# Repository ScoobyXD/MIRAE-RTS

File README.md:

MIRAE RTS

Turn everything into an rts game

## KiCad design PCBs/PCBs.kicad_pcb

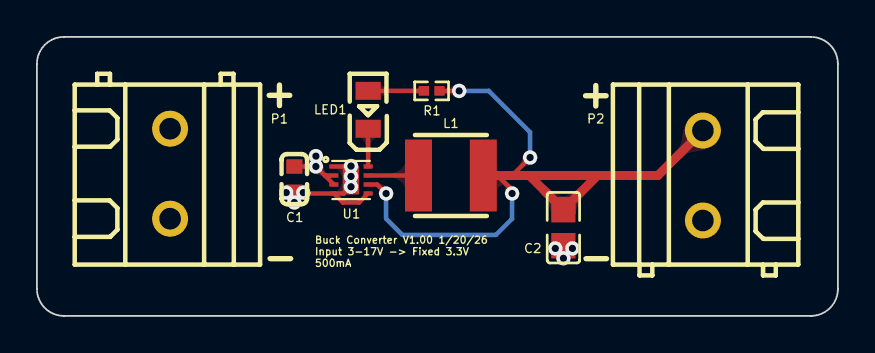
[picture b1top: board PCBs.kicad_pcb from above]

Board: 4 copper layers, 44.5 x 15.5 mm, 8 parts (0 on the bottom side), 6 nets.

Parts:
C1: 10 uF; C0603
C2: 22 uF; C0805
L1: 2.2uH; IND-SMD_L4.0-W4.0_LQH44PN2R2MP0L
LED1: Green LED; LED0805-R-RD
P1: Input 1x2; CONN-TH_2P-P5.00_WJ128V-5.0-2P
P2: Output 1x2; CONN-TH_2P-P5.00_WJ128V-5.0-2P
R1: 100k Ohms; R0402
U1: TPS62172DSGR; WSON-8_L2.0-W2.0-P0.50-TL-EP

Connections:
GND: C1.1, C2.2, P1.2, P2.1, U1.1 (PGND), U1.4 (AGND), U1.5 (FB), U1.9 (EP)
unnamed: LED1.1 (A), R1.1
unnamed: LED1.2 (K), U1.8 (PG)
unnamed: L1.2, U1.7 (SW)
VCCIN: C1.2, P1.1, U1.2 (VIN), U1.3 (EN)
VCCOUT: C2.1, L1.1, P2.2, R1.2, U1.6 (VOS)

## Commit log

2025-12-20 esp-idf hello world template
2026-01-09 Update README with project description
    Add project description to README
2026-01-09 Update project name and description in README
2026-01-09 click drag works
2026-01-11 last commit before going to internet
2026-01-19 buck converter schematic
2026-01-19 trace
2026-01-19 buck converter
2026-01-20 vias under pads and other changes
2026-01-21 changes for easyeda components
2026-01-21 should be done
2026-01-21 done
2026-01-21 buck converter done
2026-01-21 imported old wheelson stm32 project
2026-01-21 original stm32 file
2026-01-23 led on
2026-01-24 rtos led blink
2026-01-24 set clocks
2026-01-24 heartbeat 80Mhz RTOS
2026-01-25 basic i2c config, doesnt work yet
2026-01-25 what i have before clause opus
2026-01-26 i2c in progress
2026-01-27 working on i2c
2026-01-28 holy debug
2026-01-28 i2c works
2026-01-29 uart
2026-01-30 uart print not working
2026-01-30 usart works
2026-01-31 uart test
2026-02-01 fixed rtos and usart timing bug
2026-02-01 everything works up to this point
2026-02-01 the floating point is going to be a pain in the ass
2026-02-02 float stuff
2026-02-02 super ghetto usart imu print opus made the whole thing
2026-02-03 nrf9151 AT commands and GNSS works
2026-02-04 globalrts hosted on miraerts.com
2026-02-04 small edit on md files
2026-02-04 nRF9151 builds and flashes, not sure if http works
2026-02-05 raspi main compute now
2026-02-05 why did this not add in
2026-02-05 raspi api connec
2026-02-05 raspi connected
2026-02-05 change fly so it only turns on manually or upon deployment
2026-02-05 this doesnt really work save what i have now
2026-02-07 server connection works
2026-02-07 direction commands work
2026-02-08 commit for raspi
2026-02-08 anything
2026-02-08 SIM7600GH stuff
2026-02-09 example projects for SIM7600GH
2026-02-09 premade hat stuff
2026-02-09 gps working
2026-02-09 gps stuff
2026-02-09 live_gps
2026-02-09 cellular works
2026-02-10 v something
2026-02-10 dum dum merge conflict
2026-02-11 new V
2026-02-11 cellular fix
2026-02-11 fix wss
2026-02-11 my god plz fix it
2026-02-11 deleted other files not needed
2026-02-11 can bus
2026-02-13 stuff
